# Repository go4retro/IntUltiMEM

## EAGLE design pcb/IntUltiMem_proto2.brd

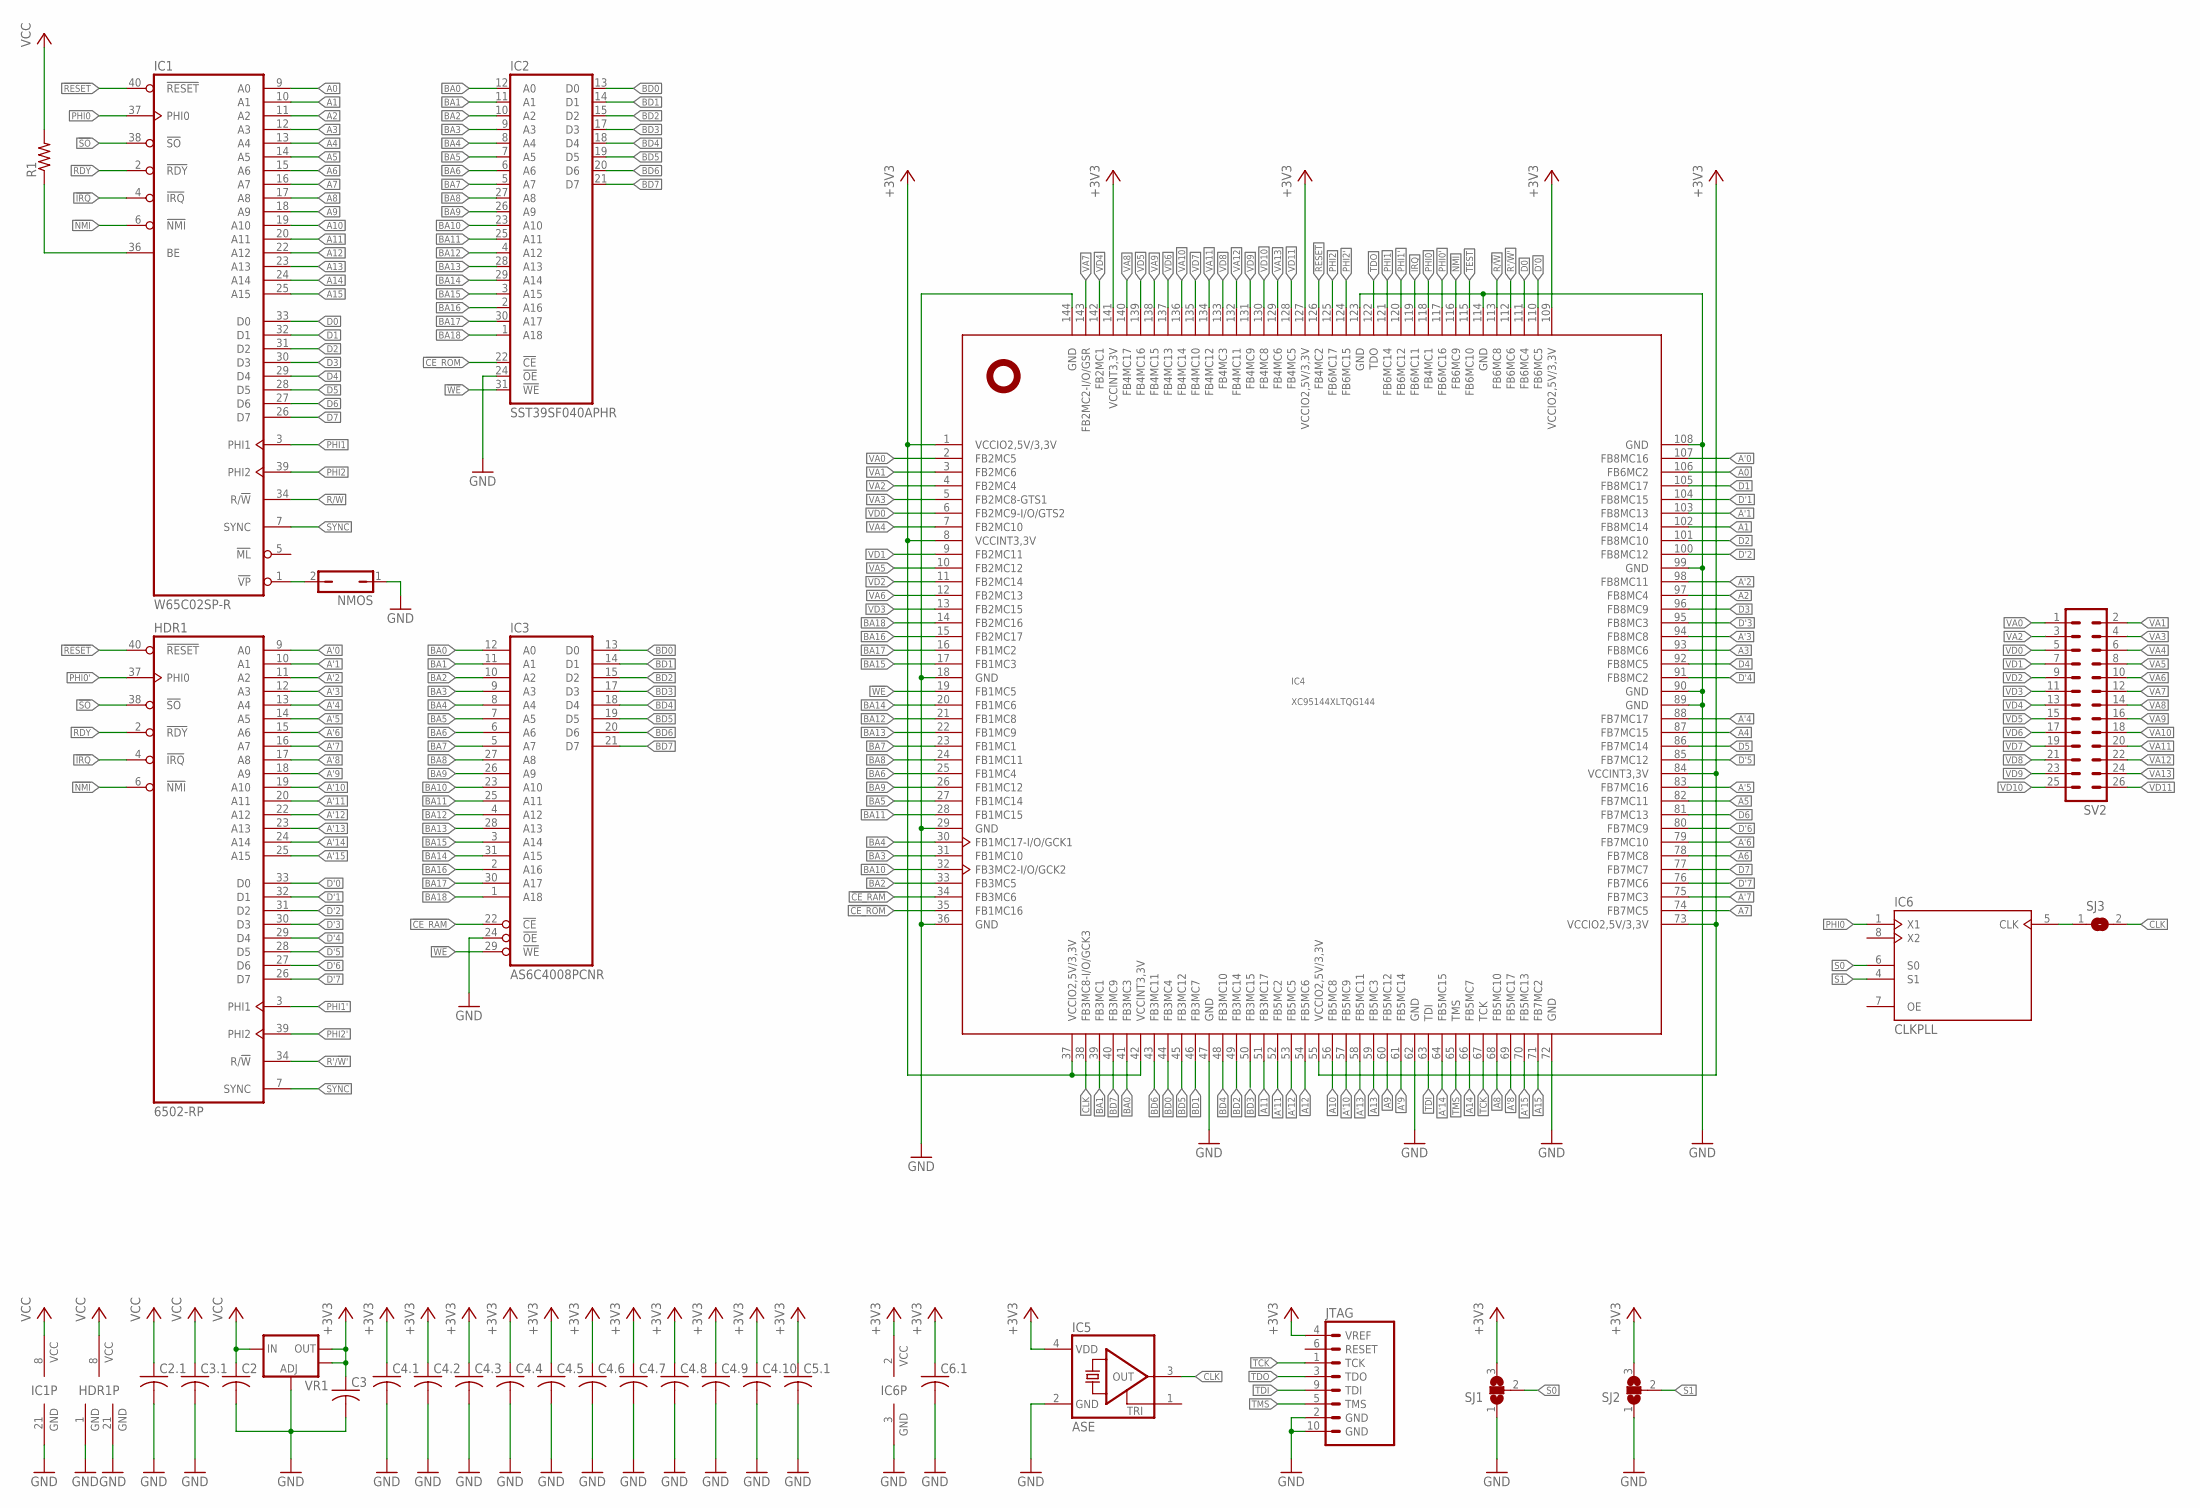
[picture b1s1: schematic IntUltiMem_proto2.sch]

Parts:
C2, C3: C-USC0805; C0805
C2.1, C3.1, C4.1, C4.2, C4.3, C4.4, C4.5, C4.6, C4.7, C4.8, C4.9, C4.10, C5.1, C6.1: C-USC0402; C0402
HDR1: 6502-RP; DIL40-ROUNDPAD
IC1: W65C02SP-R; DIL40-ROUNDPAD
IC2: SST39SF040APHR; DIL32-RP
IC3: AS6C4008PCNR; DIL32-RP
IC4: XC95144XLTQG144; TQFP144
IC5: ASE
IC6: CLKPLL; SOIC8
JTAG: JTAG
NMOS: JP1Q; JP1
R1: R-US_R0402; R0402
SJ1, SJ2: SJ2W; SJ_2
SJ3: SJ
SV2: MA13-2
VR1: V_REG_LM1117SOT223; SOT223

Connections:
!CE_RAM: IC3.22 (!CE), IC4.34 (FB3MC6)
!CE_ROM: IC2.22 (!CE), IC4.35 (FB1MC16)
!IRQ: HDR1.4 (!IRQ), IC1.4 (!IRQ), IC4.119 (FB6MC11)
!NMI: HDR1.6 (!NMI), IC1.6 (!NMI), IC4.116 (FB6MC9)
!RDY: HDR1.2 (!RDY), IC1.2 (!RDY)
!RESET: HDR1.40 (!RESET), IC1.40 (!RESET), IC4.126 (FB4MC2)
!SO: HDR1.38 (!SO), IC1.38 (!SO)
!WE: IC2.31 (!WE), IC3.29 (!WE), IC4.19 (FB1MC5)
+3V3: C3.1, C4.1.1, C4.2.1, C4.3.1, C4.4.1, C4.5.1, C4.6.1, C4.7.1, C4.8.1, C4.9.1, C4.10.1, C5.1.1, C6.1.1, IC4.1 (VCCIO2,5V/3,3V), IC4.8 (VCCINT3,3V), IC4.37 (VCCIO2,5V/3,3V), IC4.42 (VCCINT3,3V), IC4.55 (VCCIO2,5V/3,3V), IC4.73 (VCCIO2,5V/3,3V), IC4.84 (VCCINT3,3V), IC4.109 (VCCIO2,5V/3,3V), IC4.127 (VCCIO2,5V/3,3V), IC4.141 (VCCINT3,3V), IC5.4 (VDD), IC6.2 (VCC), JTAG.4 (VREF), SJ1.3, SJ2.3, VR1.2 (OUT), VR1.4 (OUT)
A0: IC1.9 (A0), IC4.106 (FB6MC2)
A1: IC1.10 (A1), IC4.102 (FB8MC14)
A2: IC1.11 (A2), IC4.97 (FB8MC4)
A3: IC1.12 (A3), IC4.93 (FB8MC6)
A4: IC1.13 (A4), IC4.87 (FB7MC15)
A5: IC1.14 (A5), IC4.82 (FB7MC11)
A6: IC1.15 (A6), IC4.78 (FB7MC8)
A7: IC1.16 (A7), IC4.74 (FB7MC5)
A8: IC1.17 (A8), IC4.68 (FB5MC10)
A9: IC1.18 (A9), IC4.60 (FB5MC12)
A10: IC1.19 (A10), IC4.56 (FB5MC8)
A11: IC1.20 (A11), IC4.51 (FB3MC17)
A12: IC1.22 (A12), IC4.54 (FB5MC6)
A13: IC1.23 (A13), IC4.59 (FB5MC3)
A14: IC1.24 (A14), IC4.66 (FB5MC7)
A15: IC1.25 (A15), IC4.71 (FB7MC2)
A'0: HDR1.9 (A0), IC4.107 (FB8MC16)
A'1: HDR1.10 (A1), IC4.103 (FB8MC13)
A'2: HDR1.11 (A2), IC4.98 (FB8MC11)
A'3: HDR1.12 (A3), IC4.94 (FB8MC8)
A'4: HDR1.13 (A4), IC4.88 (FB7MC17)
A'5: HDR1.14 (A5), IC4.83 (FB7MC16)
A'6: HDR1.15 (A6), IC4.79 (FB7MC10)
A'7: HDR1.16 (A7), IC4.75 (FB7MC3)
A'8: HDR1.17 (A8), IC4.69 (FB5MC17)
A'9: HDR1.18 (A9), IC4.61 (FB5MC14)
A'10: HDR1.19 (A10), IC4.57 (FB5MC9)
A'11: HDR1.20 (A11), IC4.52 (FB5MC2)
A'12: HDR1.22 (A12), IC4.53 (FB5MC5)
A'13: HDR1.23 (A13), IC4.58 (FB5MC11)
A'14: HDR1.24 (A14), IC4.64 (FB5MC15)
A'15: HDR1.25 (A15), IC4.70 (FB5MC13)
BA0: IC2.12 (A0), IC3.12 (A0), IC4.41 (FB3MC3)
BA1: IC2.11 (A1), IC3.11 (A1), IC4.39 (FB3MC1)
BA2: IC2.10 (A2), IC3.10 (A2), IC4.33 (FB3MC5)
BA3: IC2.9 (A3), IC3.9 (A3), IC4.31 (FB1MC10)
BA4: IC2.8 (A4), IC3.8 (A4), IC4.30 (FB1MC17-I/O/GCK1)
BA5: IC2.7 (A5), IC3.7 (A5), IC4.27 (FB1MC14)
BA6: IC2.6 (A6), IC3.6 (A6), IC4.25 (FB1MC4)
BA7: IC2.5 (A7), IC3.5 (A7), IC4.23 (FB1MC1)
BA8: IC2.27 (A8), IC3.27 (A8), IC4.24 (FB1MC11)
BA9: IC2.26 (A9), IC3.26 (A9), IC4.26 (FB1MC12)
BA10: IC2.23 (A10), IC3.23 (A10), IC4.32 (FB3MC2-I/O/GCK2)
BA11: IC2.25 (A11), IC3.25 (A11), IC4.28 (FB1MC15)
BA12: IC2.4 (A12), IC3.4 (A12), IC4.21 (FB1MC8)
BA13: IC2.28 (A13), IC3.28 (A13), IC4.22 (FB1MC9)
BA14: IC2.29 (A14), IC3.31 (A15), IC4.20 (FB1MC6)
BA15: IC2.3 (A15), IC3.3 (A14), IC4.17 (FB1MC3)
BA16: IC2.2 (A16), IC3.2 (A16), IC4.15 (FB2MC17)
BA17: IC2.30 (A17), IC3.30 (A17), IC4.16 (FB1MC2)
BA18: IC2.1 (A18), IC3.1 (A18), IC4.14 (FB2MC16)
BD0: IC2.13 (D0), IC3.13 (D0), IC4.44 (FB3MC4)
BD1: IC2.14 (D1), IC3.14 (D1), IC4.46 (FB3MC7)
BD2: IC2.15 (D2), IC3.15 (D2), IC4.49 (FB3MC14)
BD3: IC2.17 (D3), IC3.17 (D3), IC4.50 (FB3MC15)
BD4: IC2.18 (D4), IC3.18 (D4), IC4.48 (FB3MC10)
BD5: IC2.19 (D5), IC3.19 (D5), IC4.45 (FB3MC12)
BD6: IC2.20 (D6), IC3.20 (D6), IC4.43 (FB3MC11)
BD7: IC2.21 (D7), IC3.21 (D7), IC4.40 (FB3MC9)
CLK: IC4.38 (FB3MC8-I/O/GCK3), IC5.3 (OUT), SJ3.2
D0: IC1.33 (D0), IC4.111 (FB6MC4)
D1: IC1.32 (D1), IC4.105 (FB8MC17)
D2: IC1.31 (D2), IC4.101 (FB8MC10)
D3: IC1.30 (D3), IC4.96 (FB8MC9)
D4: IC1.29 (D4), IC4.92 (FB8MC5)
D5: IC1.28 (D5), IC4.86 (FB7MC14)
D6: IC1.27 (D6), IC4.81 (FB7MC13)
D7: IC1.26 (D7), IC4.77 (FB7MC7)
D'0: HDR1.33 (D0), IC4.110 (FB6MC5)
D'1: HDR1.32 (D1), IC4.104 (FB8MC15)
D'2: HDR1.31 (D2), IC4.100 (FB8MC12)
D'3: HDR1.30 (D3), IC4.95 (FB8MC3)
D'4: HDR1.29 (D4), IC4.91 (FB8MC2)
D'5: HDR1.28 (D5), IC4.85 (FB7MC12)
D'6: HDR1.27 (D6), IC4.80 (FB7MC9)
D'7: HDR1.26 (D7), IC4.76 (FB7MC6)
GND: C2.2, C2.1.2, C3.2, C3.1.2, C4.1.2, C4.2.2, C4.3.2, C4.4.2, C4.5.2, C4.6.2, C4.7.2, C4.8.2, C4.9.2, C4.10.2, C5.1.2, C6.1.2, HDR1.1 (GND), HDR1.21 (GND), IC1.21 (GND), IC2.16 (GND), IC2.24 (!OE), IC3.16 (GND), IC3.24 (!OE), IC4.18 (GND), IC4.29 (GND), IC4.36 (GND), IC4.47 (GND), IC4.62 (GND), IC4.72 (GND), IC4.89 (GND), IC4.90 (GND), IC4.99 (GND), IC4.108 (GND), IC4.114 (GND), IC4.123 (GND), IC4.144 (GND), IC5.2 (GND), IC6.3 (GND), JTAG.2 (GND), JTAG.10 (GND), NMOS.1, SJ1.1, SJ2.1, VR1.1 (ADJ)
unnamed: IC1.36 (BE), R1.1
unnamed: IC1.1 (!VP), NMOS.2
unnamed: IC6.5 (CLK), SJ3.1
PHI0: IC1.37 (PHI0), IC4.118 (FB4MC1), IC6.1 (X1)
PHI0': HDR1.37 (PHI0), IC4.117 (FB6MC16)
PHI1: IC1.3 (PHI1), IC4.121 (FB6MC14)
PHI1': HDR1.3 (PHI1), IC4.120 (FB6MC12)
PHI2: IC1.39 (PHI2), IC4.125 (FB6MC17)
PHI2': HDR1.39 (PHI2), IC4.124 (FB6MC15)
R'/!W': HDR1.34 (R/!W), IC4.112 (FB6MC6)
R/!W: IC1.34 (R/!W), IC4.113 (FB6MC8)
S0: IC6.6 (S0), SJ1.2
S1: IC6.4 (S1), SJ2.2
SYNC: HDR1.7 (SYNC), IC1.7 (SYNC)
TCK: IC4.67 (TCK), JTAG.1 (TCK)
TDI: IC4.63 (TDI), JTAG.9 (TDI)
TDO: IC4.122 (TDO), JTAG.3 (TDO)
TEST: IC4.115 (FB6MC10)
TMS: IC4.65 (TMS), JTAG.5 (TMS)
VA0: IC4.2 (FB2MC5), SV2.1
VA1: IC4.3 (FB2MC6), SV2.2
VA2: IC4.4 (FB2MC4), SV2.3
VA3: IC4.5 (FB2MC8-GTS1), SV2.4
VA4: IC4.7 (FB2MC10), SV2.6
VA5: IC4.10 (FB2MC12), SV2.8
VA6: IC4.12 (FB2MC13), SV2.10
VA7: IC4.143 (FB2MC2-I/O/GSR), SV2.12
VA8: IC4.140 (FB4MC17), SV2.14
VA9: IC4.138 (FB4MC15), SV2.16
VA10: IC4.136 (FB4MC14), SV2.18
VA11: IC4.134 (FB4MC12), SV2.20
VA12: IC4.132 (FB4MC11), SV2.22
VA13: IC4.129 (FB4MC6), SV2.24
VCC: C2.1, C2.1.1, C3.1.1, HDR1.8 (VCC), IC1.8 (VCC), IC2.32 (VCC), IC3.32 (VCC), R1.2, VR1.3 (IN)
VD0: IC4.6 (FB2MC9-I/O/GTS2), SV2.5
VD1: IC4.9 (FB2MC11), SV2.7
VD2: IC4.11 (FB2MC14), SV2.9
VD3: IC4.13 (FB2MC15), SV2.11
VD4: IC4.142 (FB2MC1), SV2.13
VD5: IC4.139 (FB4MC16), SV2.15
VD6: IC4.137 (FB4MC13), SV2.17
VD7: IC4.135 (FB4MC10), SV2.19
VD8: IC4.133 (FB4MC3), SV2.21
VD9: IC4.131 (FB4MC9), SV2.23
VD10: IC4.130 (FB4MC8), SV2.25
VD11: IC4.128 (FB4MC5), SV2.26

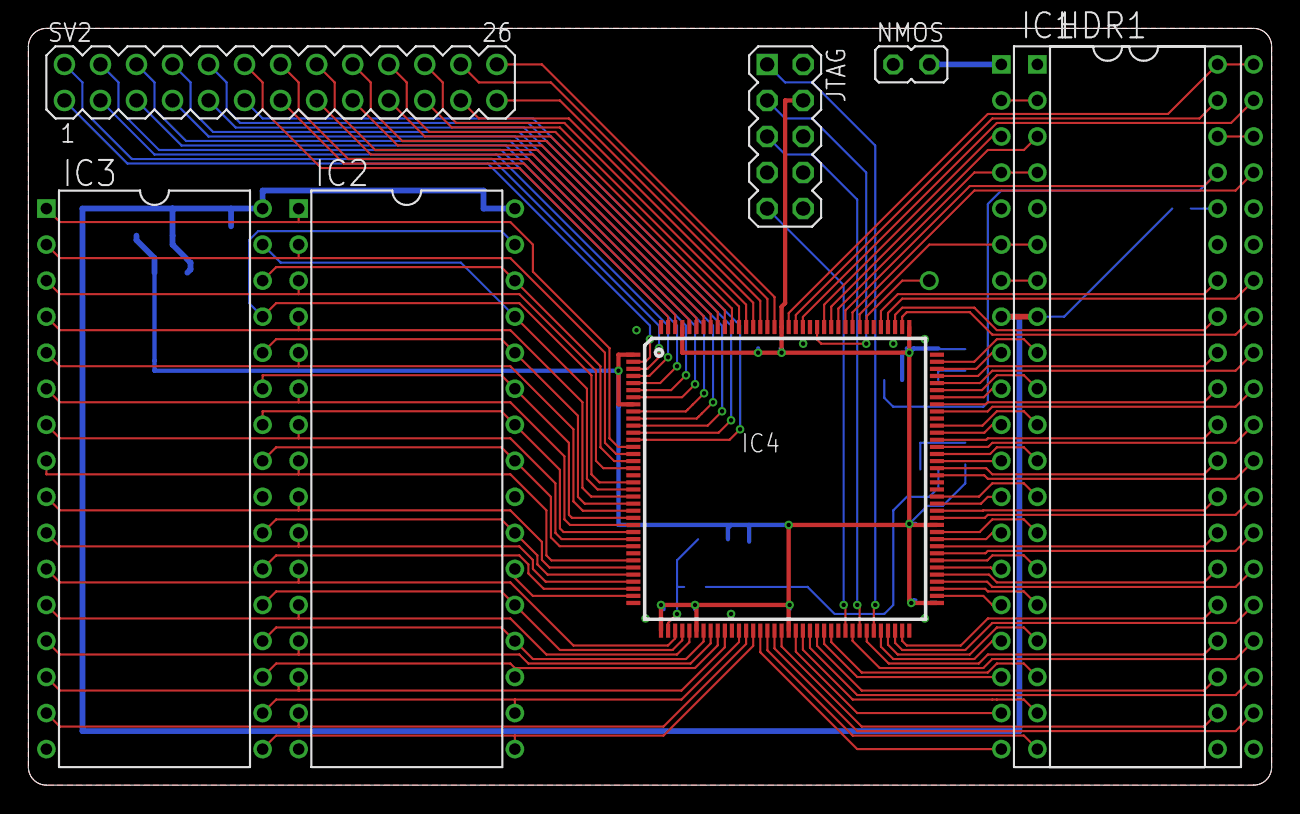
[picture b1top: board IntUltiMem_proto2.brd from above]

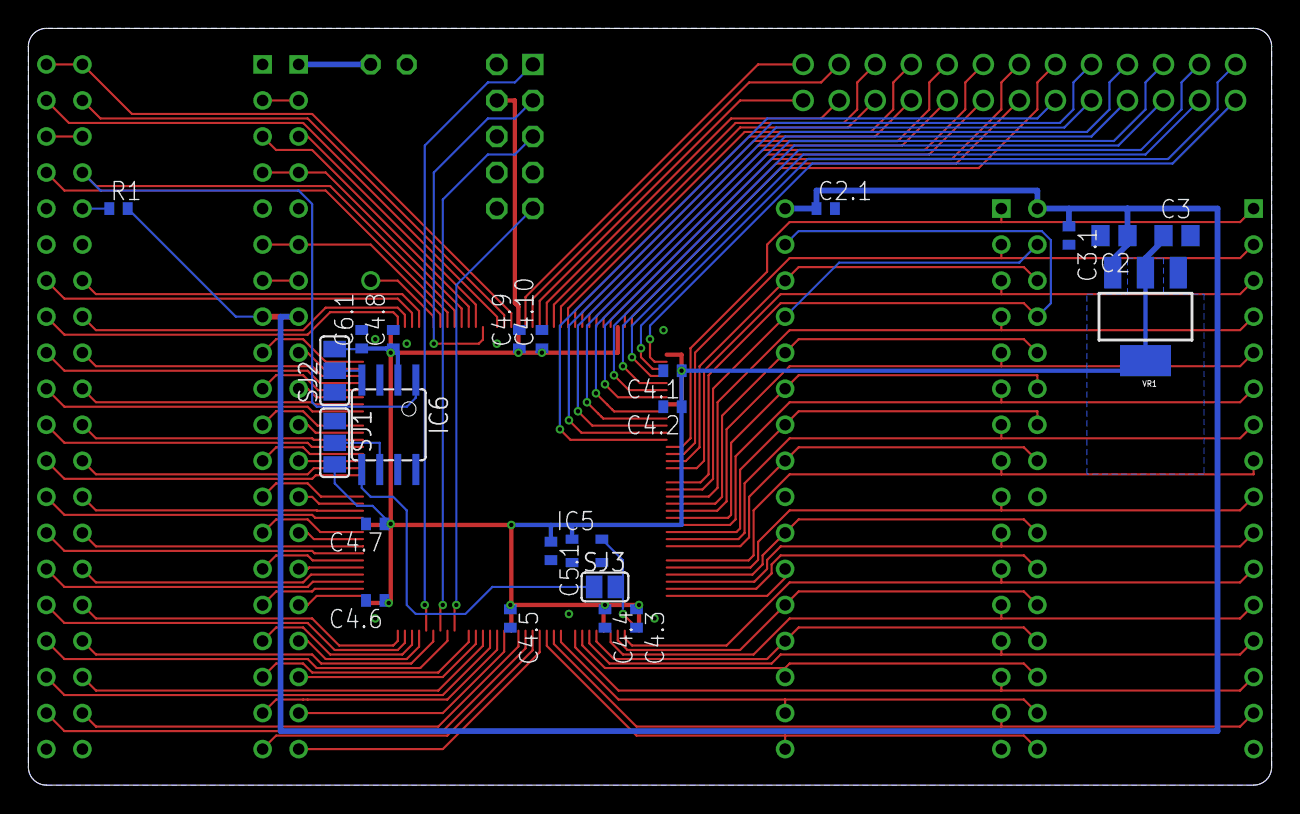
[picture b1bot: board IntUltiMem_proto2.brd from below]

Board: 2 copper layers, 87.6 x 53.3 mm, 31 parts (23 on the bottom side), 131 nets.

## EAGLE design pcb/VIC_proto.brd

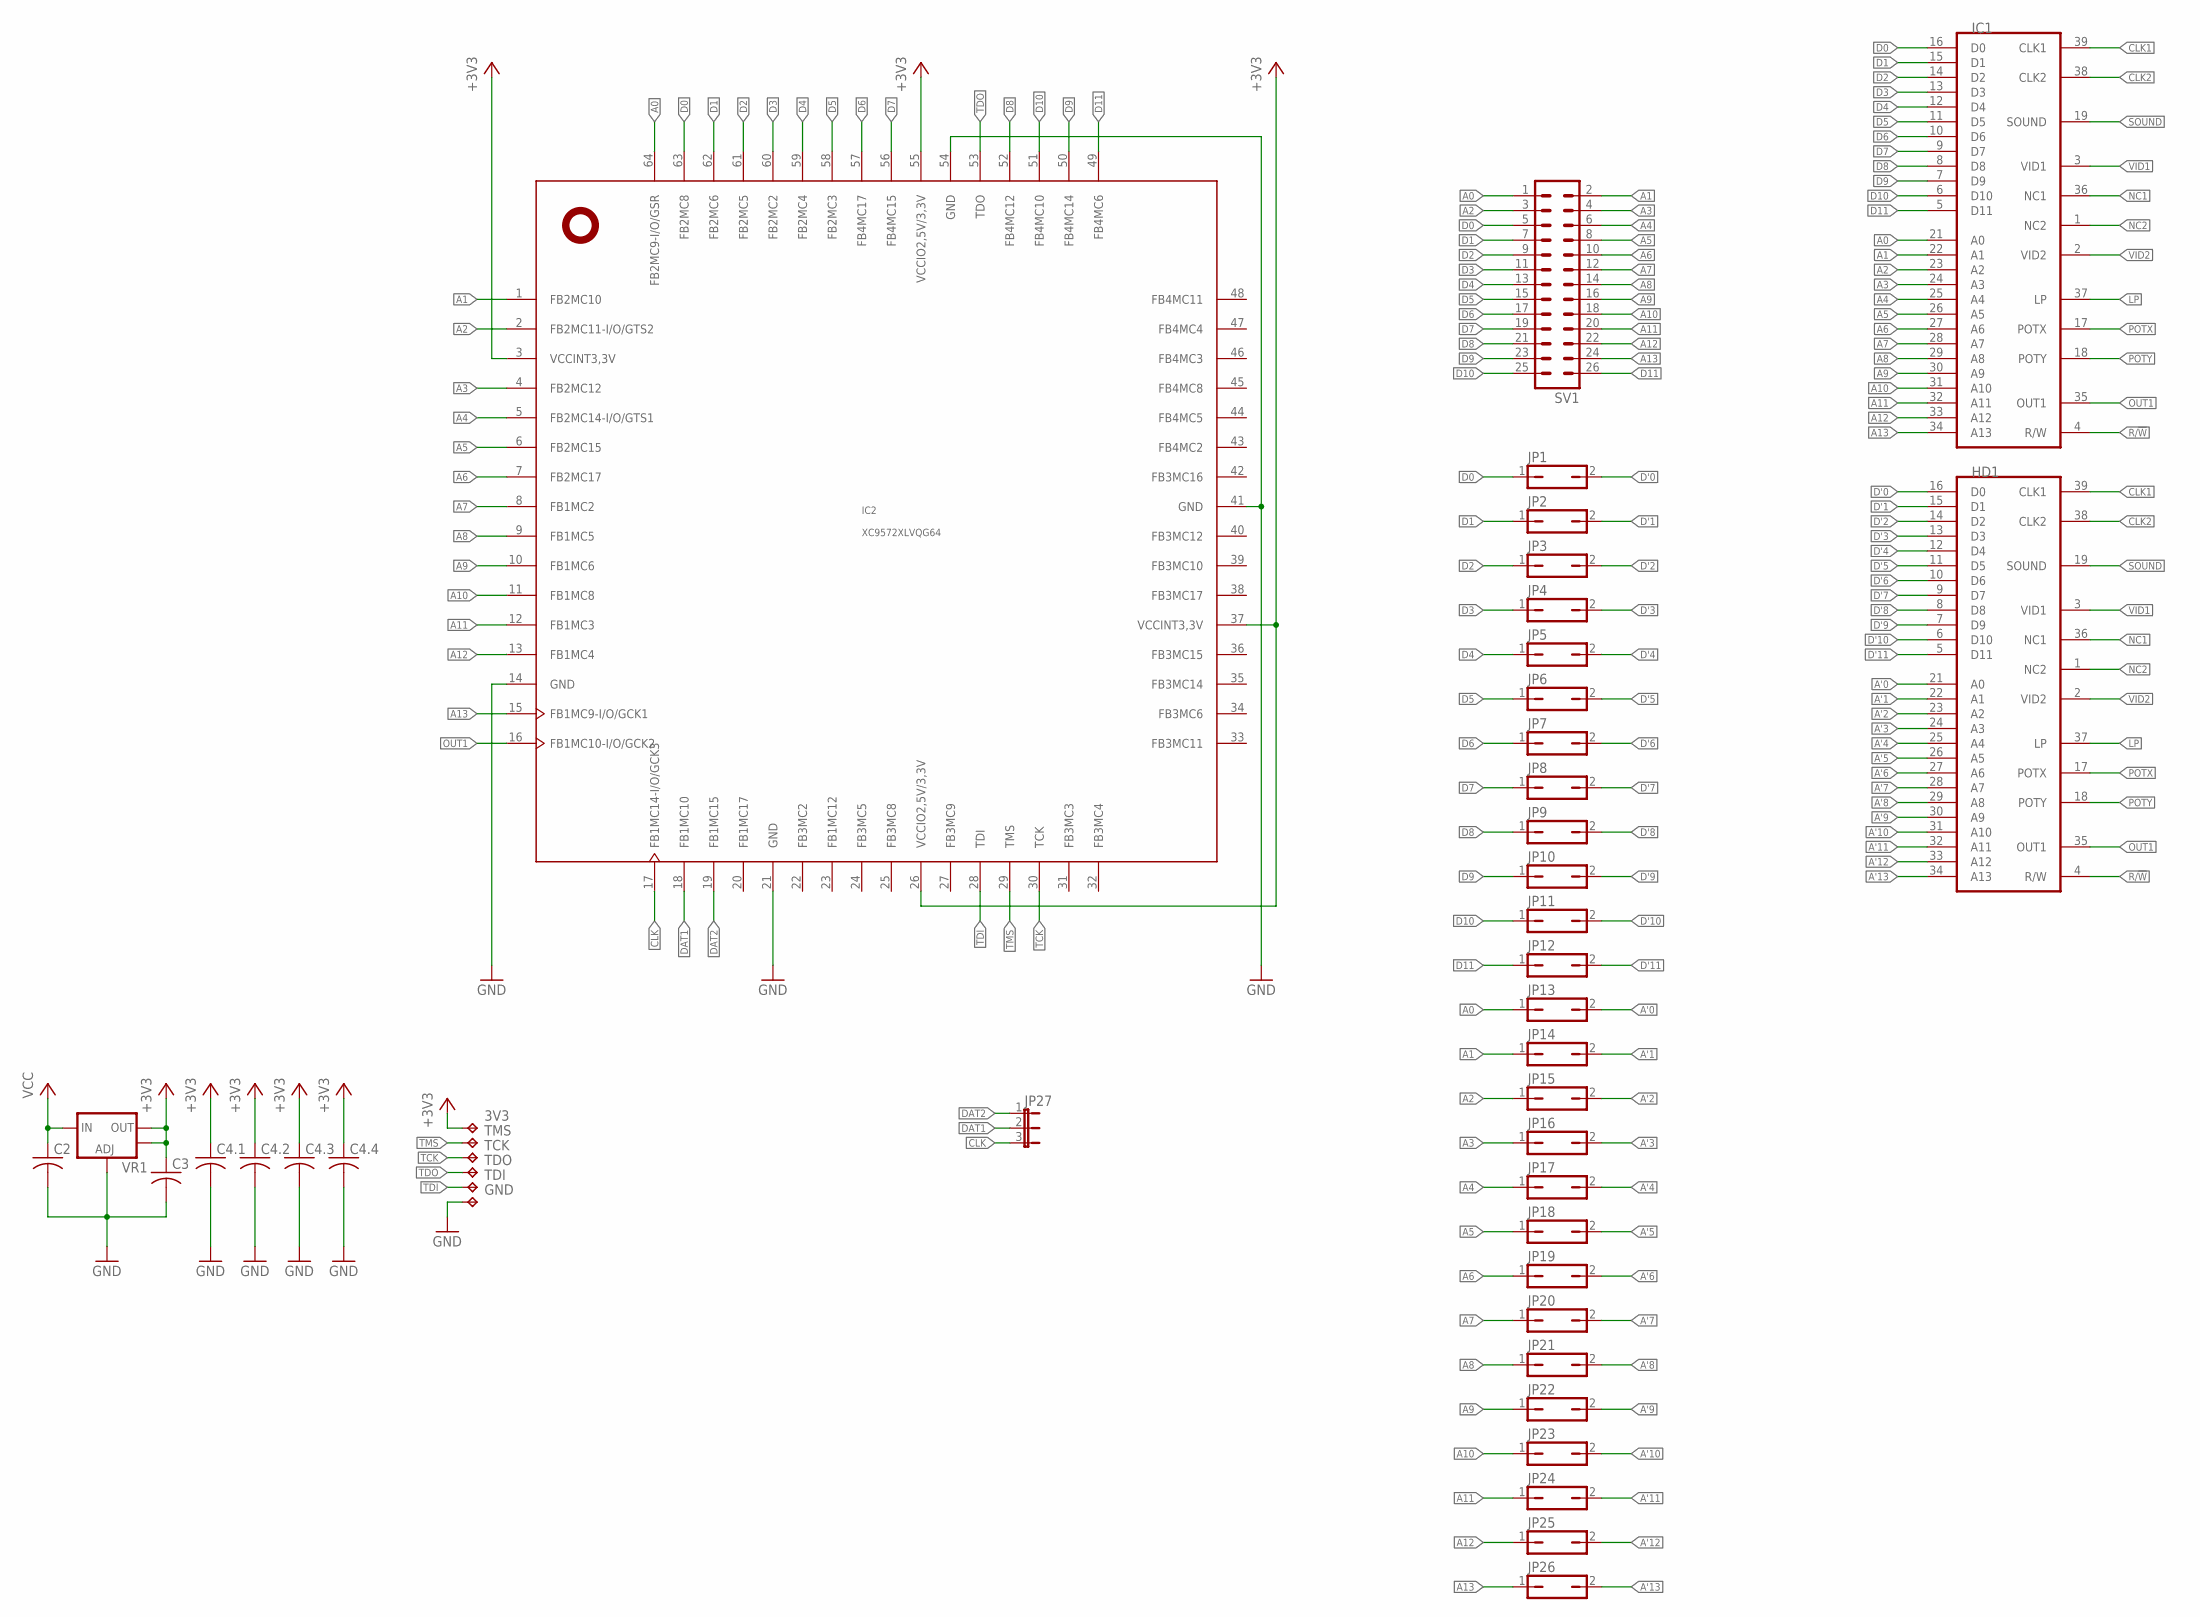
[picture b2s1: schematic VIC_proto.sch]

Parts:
3V3: TPTP09R; TP09R
C2, C3: C-USC0805; C0805
C4.1, C4.2, C4.3, C4.4: C-USC0402; C0402
GND: TPTP10R; TP10R
HD1: 6560-RP; DIL40-ROUNDPAD
IC1: 6560-RP; DIL40-ROUNDPAD
IC2: XC9572XLVQG64; VQFP64
JP1, JP2, JP3, JP4, JP5, JP6, JP7, JP8, JP9, JP10, JP11, JP12, JP13, JP14, JP15, JP16, JP17, JP18, JP19, JP20, JP21, JP22, JP23, JP24, JP25, JP26: JP1Q; JP1
JP27: JP2E; JP2
SV1: MA13-2
TCK: TPTP09R; TP09R
TDI: TPTP09R; TP09R
TDO: TPTP09R; TP09R
TMS: TPTP09R; TP09R
VR1: V_REG_LM1117SOT223; SOT223

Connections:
+3V3: 3V3.TP, C3.1, C4.1.1, C4.2.1, C4.3.1, C4.4.1, IC2.3 (VCCINT3,3V), IC2.26 (VCCIO2,5V/3,3V), IC2.37 (VCCINT3,3V), IC2.55 (VCCIO2,5V/3,3V), VR1.2 (OUT), VR1.4 (OUT)
A0: IC1.21 (A0), IC2.64 (FB2MC9-I/O/GSR), JP13.1, SV1.1
A1: IC1.22 (A1), IC2.1 (FB2MC10), JP14.1, SV1.2
A2: IC1.23 (A2), IC2.2 (FB2MC11-I/O/GTS2), JP15.1, SV1.3
A3: IC1.24 (A3), IC2.4 (FB2MC12), JP16.1, SV1.4
A4: IC1.25 (A4), IC2.5 (FB2MC14-I/O/GTS1), JP17.1, SV1.6
A5: IC1.26 (A5), IC2.6 (FB2MC15), JP18.1, SV1.8
A6: IC1.27 (A6), IC2.7 (FB2MC17), JP19.1, SV1.10
A7: IC1.28 (A7), IC2.8 (FB1MC2), JP20.1, SV1.12
A8: IC1.29 (A8), IC2.9 (FB1MC5), JP21.1, SV1.14
A9: IC1.30 (A9), IC2.10 (FB1MC6), JP22.1, SV1.16
A10: IC1.31 (A10), IC2.11 (FB1MC8), JP23.1, SV1.18
A11: IC1.32 (A11), IC2.12 (FB1MC3), JP24.1, SV1.20
A12: IC1.33 (A12), IC2.13 (FB1MC4), JP25.1, SV1.22
A13: IC1.34 (A13), IC2.15 (FB1MC9-I/O/GCK1), JP26.1, SV1.24
A'0: HD1.21 (A0), JP13.2
A'1: HD1.22 (A1), JP14.2
A'2: HD1.23 (A2), JP15.2
A'3: HD1.24 (A3), JP16.2
A'4: HD1.25 (A4), JP17.2
A'5: HD1.26 (A5), JP18.2
A'6: HD1.27 (A6), JP19.2
A'7: HD1.28 (A7), JP20.2
A'8: HD1.29 (A8), JP21.2
A'9: HD1.30 (A9), JP22.2
A'10: HD1.31 (A10), JP23.2
A'11: HD1.32 (A11), JP24.2
A'12: HD1.33 (A12), JP25.2
A'13: HD1.34 (A13), JP26.2
CLK: IC2.17 (FB1MC14-I/O/GCK3), JP27.3
CLK1: HD1.39 (CLK1), IC1.39 (CLK1)
CLK2: HD1.38 (CLK2), IC1.38 (CLK2)
D0: IC1.16 (D0), IC2.63 (FB2MC8), JP1.1, SV1.5
D1: IC1.15 (D1), IC2.62 (FB2MC6), JP2.1, SV1.7
D2: IC1.14 (D2), IC2.61 (FB2MC5), JP3.1, SV1.9
D3: IC1.13 (D3), IC2.60 (FB2MC2), JP4.1, SV1.11
D4: IC1.12 (D4), IC2.59 (FB2MC4), JP5.1, SV1.13
D5: IC1.11 (D5), IC2.58 (FB2MC3), JP6.1, SV1.15
D6: IC1.10 (D6), IC2.57 (FB4MC17), JP7.1, SV1.17
D7: IC1.9 (D7), IC2.56 (FB4MC15), JP8.1, SV1.19
D8: IC1.8 (D8), IC2.52 (FB4MC12), JP9.1, SV1.21
D9: IC1.7 (D9), IC2.50 (FB4MC14), JP10.1, SV1.23
D10: IC1.6 (D10), IC2.51 (FB4MC10), JP11.1, SV1.25
D11: IC1.5 (D11), IC2.49 (FB4MC6), JP12.1, SV1.26
D'0: HD1.16 (D0), JP1.2
D'1: HD1.15 (D1), JP2.2
D'2: HD1.14 (D2), JP3.2
D'3: HD1.13 (D3), JP4.2
D'4: HD1.12 (D4), JP5.2
D'5: HD1.11 (D5), JP6.2
D'6: HD1.10 (D6), JP7.2
D'7: HD1.9 (D7), JP8.2
D'8: HD1.8 (D8), JP9.2
D'9: HD1.7 (D9), JP10.2
D'10: HD1.6 (D10), JP11.2
D'11: HD1.5 (D11), JP12.2
DAT1: IC2.18 (FB1MC10), JP27.2
DAT2: IC2.19 (FB1MC15), JP27.1
GND: C2.2, C3.2, C4.1.2, C4.2.2, C4.3.2, C4.4.2, GND.TP, HD1.20 (GND), IC1.20 (GND), IC2.14 (GND), IC2.21 (GND), IC2.41 (GND), IC2.54 (GND), VR1.1 (ADJ)
LP: HD1.37 (LP), IC1.37 (LP)
NC1: HD1.36 (NC1), IC1.36 (NC1)
NC2: HD1.1 (NC2), IC1.1 (NC2)
OUT1: HD1.35 (OUT1), IC1.35 (OUT1), IC2.16 (FB1MC10-I/O/GCK2)
POTX: HD1.17 (POTX), IC1.17 (POTX)
POTY: HD1.18 (POTY), IC1.18 (POTY)
R/!W: HD1.4 (R/W), IC1.4 (R/W)
SOUND: HD1.19 (SOUND), IC1.19 (SOUND)
TCK: IC2.30 (TCK), TCK.TP
TDI: IC2.28 (TDI), TDI.TP
TDO: IC2.53 (TDO), TDO.TP
TMS: IC2.29 (TMS), TMS.TP
VCC: C2.1, HD1.40 (VCC), IC1.40 (VCC), VR1.3 (IN)
VID1: HD1.3 (VID1), IC1.3 (VID1)
VID2: HD1.2 (VID2), IC1.2 (VID2)

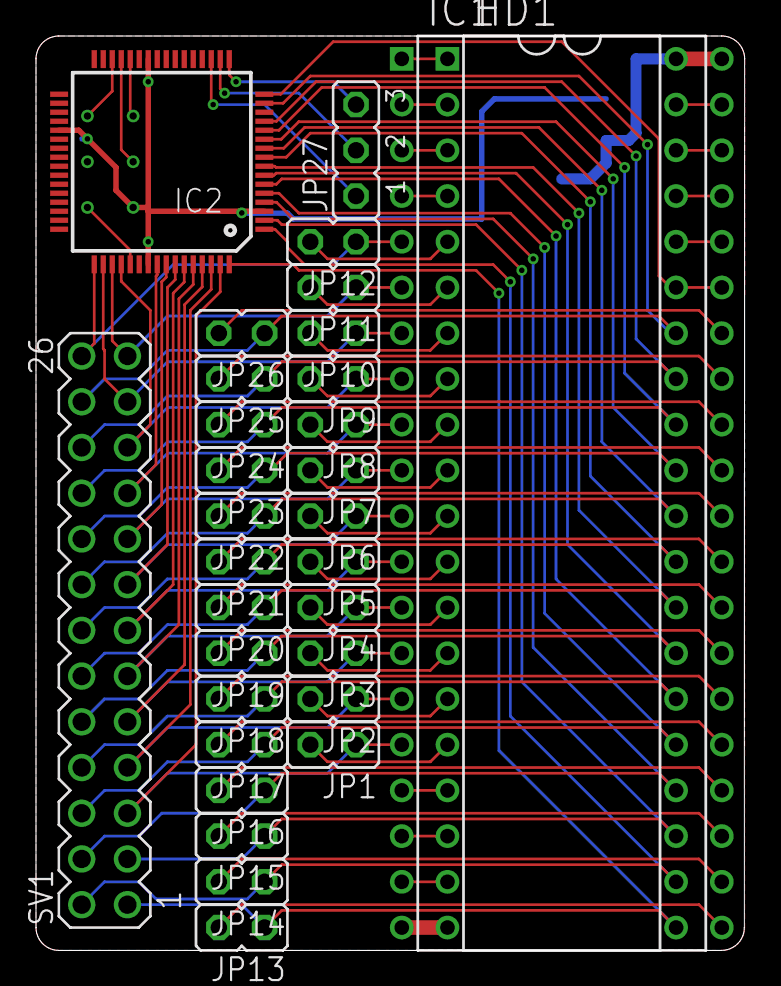
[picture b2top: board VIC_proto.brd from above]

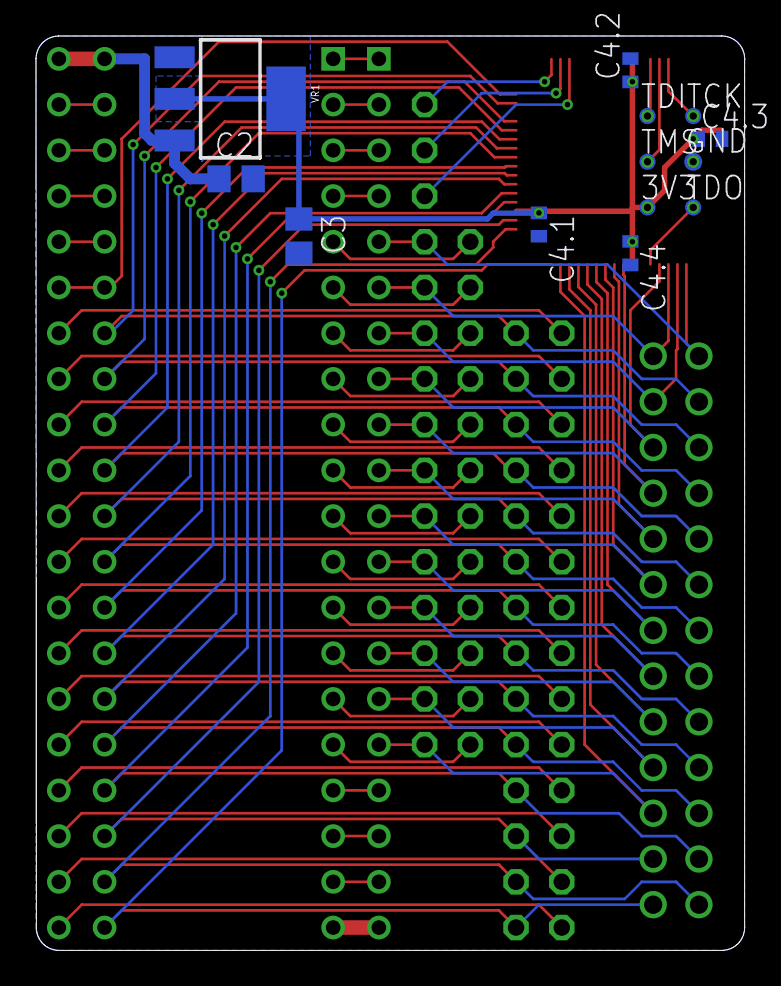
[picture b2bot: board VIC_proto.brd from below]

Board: 2 copper layers, 39.4 x 50.8 mm, 44 parts (13 on the bottom side), 74 nets.

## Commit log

2020-05-14 Switch to sending internally generated clock signals and remove unused s01 signal

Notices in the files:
parts and their libraries:
SparkFun: Licensing: CC v3.0 Share-Alike You are welcome to use this library for commercial purposes.
